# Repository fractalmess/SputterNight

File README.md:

# SputterNight
Consolidated efforts towards refurbishing a Edwards 306 sputter tool in oakland Ca

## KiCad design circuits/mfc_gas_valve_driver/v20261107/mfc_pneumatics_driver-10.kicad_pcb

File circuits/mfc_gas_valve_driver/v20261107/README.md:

Update to the MFC, front panel and pneumatic valve driver and interface circuit.
Analog support for the Tylan MFC added.

KiCad 10.0 used with this circuit.

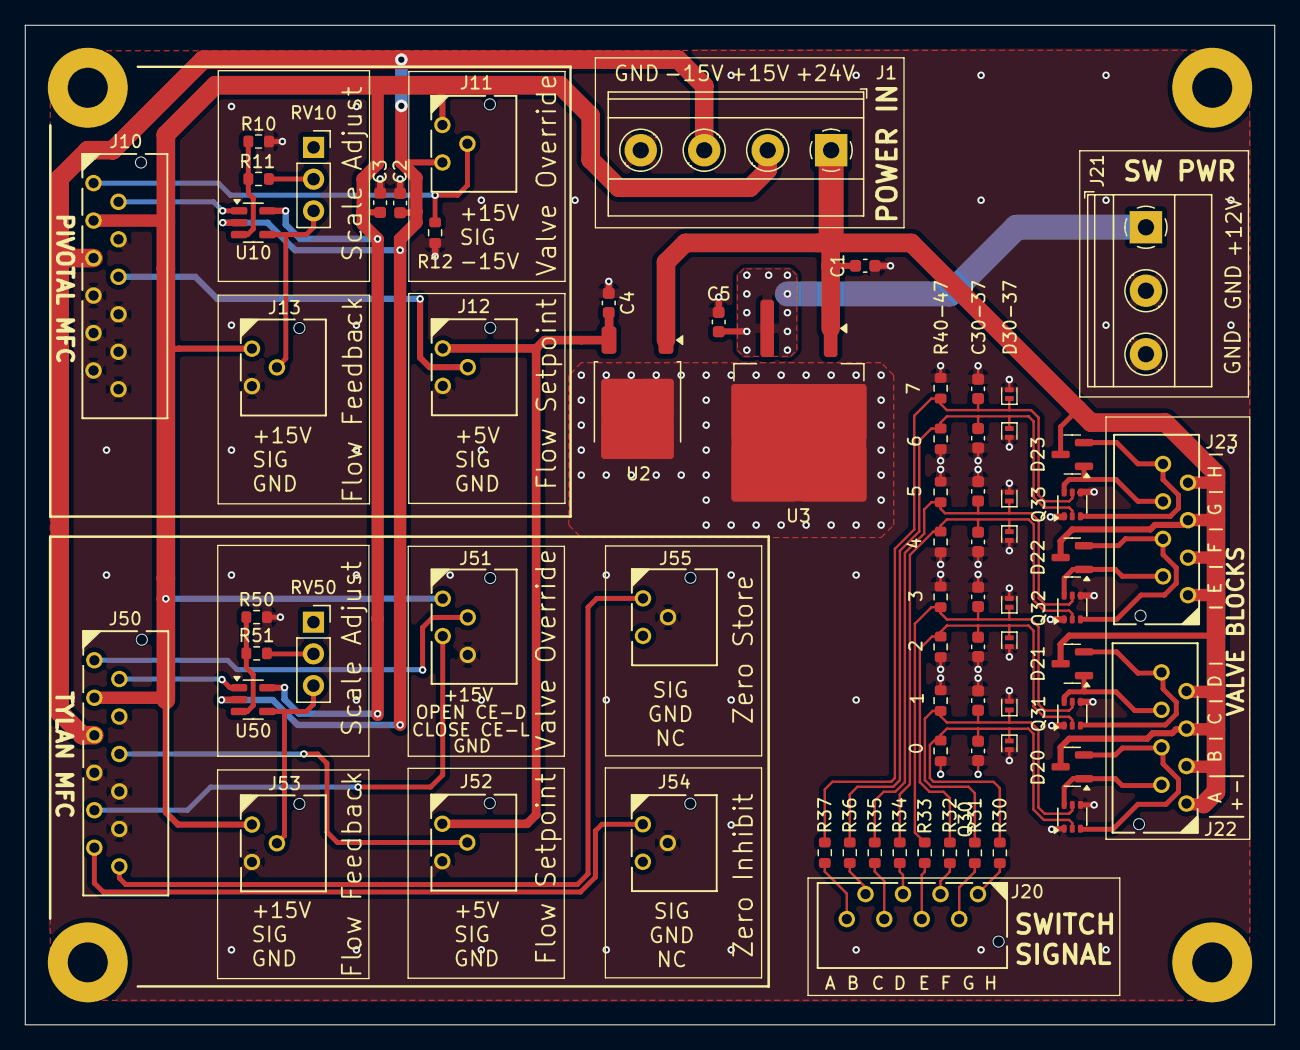
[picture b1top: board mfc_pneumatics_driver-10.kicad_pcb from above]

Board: 2 copper layers, 100.0 x 80.0 mm, 76 parts (1 on the bottom side), 45 nets.

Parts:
**REF: rfix_logo
C1, C2, C3, C4, C5: 1u 50V X7R; C_0603_1608Metric
C30, C31, C32, C33, C34, C35, C36, C37: C; C_0603_1608Metric
D20, D21, D22, D23: BAT54C; SOT-23
D30, D31, D32, D33, D34, D35, D36, D37: DF2S16CT; D_SOD-882
H1, H2, H3, H4: MountingHole_Pad; MountingHole_3.2mm_M3_Pad
J1: Screw_Terminal_01x04; TerminalBlock_Phoenix_MKDS-1,5-4-5.08_1x04_P5.08mm_Horizont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
J10, J50: Conn_01x12_Socket; Molex_CLIK-Mate_50315908_1x12-1MP_P1.50mm_Vertical
J11, J12, J13, J52, J53, J54, J55: Conn_01x03_Socket; Molex_CLIK-Mate_50315908_1x03-1MP_P1.50mm_Vertical
J20, J22, J23: Conn_01x08_Socket; Molex_CLIK-Mate_50315908_1x08-1MP_P1.50mm_Vertical
J21: Screw_Terminal_01x03; TerminalBlock_Phoenix_MKDS-1,5-3-5.08_1x03_P5.08mm_Horizont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
J51: Conn_01x04_Socket; Molex_CLIK-Mate_50315908_1x04-1MP_P1.50mm_Vertical
Q30, Q31, Q32, Q33: SSM6N7002KFU; SOT-363_SC-70-6
R10, R50: 1k; R_0603_1608Metric
R11, R51: 953R; R_0603_1608Metric
R12, R40, R41, R42, R43, R44, R45, R46, R47: 10k; R_0603_1608Metric
R30, R31, R32, R33, R34, R35, R36, R37: 10R; R_0603_1608Metric
RV10, RV50: 100R; PinSocket_1x03_P2.54mm_Vertical
U2: MC78M05_TO252; TO-252-2
U3: MC7812-TO263; TO-263-2
U10, U50: LM321; SOT-23-5

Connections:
+5V: C4.1, J12.1, J52.1, U2.3 (VO)
+12V: C5.1, J21.1, U3.3 (VO)
+15V: C3.1, J1.2, J10.3, J11.1, J13.1, J50.3, J51.1, J53.1, U10.5 (V+), U50.5 (V+)
+24V: C1.1, D20.3, D21.3, D22.3, D23.3, J1.1, J22.1, J22.3, J22.5, J22.7, J23.1, J23.3, J23.5, J23.7, U2.1 (VI), U3.1 (VI)
-15V: C2.2, J1.3, J10.5, J11.3, J50.5, U10.2 (V-), U50.2 (V-)
/SW1: J20.1, R30.1
/SW2: J20.2, R31.1
/SW3: J20.3, R32.1
/SW4: J20.4, R33.1
/SW5: J20.5, R34.1
/SW6: J20.6, R35.1
/SW7: J20.7, R36.1
/SW8: J20.8, R37.1
/valve_driver_1/V1_RETURN: D20.1, J22.2, Q30.6 (D)
/valve_driver_1/V2_RETURN: D20.2, J22.4, Q30.3 (D)
/valve_driver_2/V1_RETURN: D21.1, J22.6, Q31.6 (D)
/valve_driver_2/V2_RETURN: D21.2, J22.8, Q31.3 (D)
/valve_driver_3/V1_RETURN: D22.1, J23.2, Q32.6 (D)
/valve_driver_3/V2_RETURN: D22.2, J23.4, Q32.3 (D)
/valve_driver_4/V1_RETURN: D23.1, J23.6, Q33.6 (D)
/valve_driver_4/V2_RETURN: D23.2, J23.8, Q33.3 (D)
GND: C1.2, C2.1, C3.2, C4.2, C5.2, C30.2, C31.2, C32.2, C33.2, C34.2, C35.2, C36.2, C37.2, D30.2 (A), D31.2 (A), D32.2 (A), D33.2 (A), D34.2 (A), D35.2 (A), D36.2 (A), D37.2 (A), J1.4, J10.4, J10.7, J10.8, J10.9, J10.10, J10.11, J10.12, J12.3, J13.3, J21.2, J21.3, J50.4, J50.7, J50.8, J50.10, J51.4, J52.3, J53.3, J54.2, J55.2, Q30.1 (S), Q30.4 (S), Q31.1 (S), Q31.4 (S), Q32.1 (S), Q32.4 (S), Q33.1 (S), Q33.4 (S), R10.1, R12.2, R40.1, R41.1, R42.1, R43.1, R44.1, R45.1, R46.1, R47.1, R50.1, U2.2 (GND), U3.2 (GND)
unnamed: C30.1, D30.1 (K), Q30.2 (G), R30.2, R40.2
unnamed: C31.1, D31.1 (K), Q30.5 (G), R31.2, R41.2
unnamed: C32.1, D32.1 (K), Q31.2 (G), R32.2, R42.2
unnamed: C33.1, D33.1 (K), Q31.5 (G), R33.2, R43.2
unnamed: C34.1, D34.1 (K), Q32.2 (G), R34.2, R44.2
unnamed: C35.1, D35.1 (K), Q32.5 (G), R35.2, R45.2
unnamed: C36.1, D36.1 (K), Q33.2 (G), R36.2, R46.2
unnamed: C37.1, D37.1 (K), Q33.5 (G), R37.2, R47.2
unnamed: J10.1, J11.2, R12.1
unnamed: J10.2, U10.1 (+)
unnamed: J10.6, J12.2
unnamed: J13.2, RV10.3, U10.4
unnamed: J50.1, J51.2
unnamed: J50.2, U50.1 (+)
unnamed: J50.6, J52.2
unnamed: J50.9, J51.3
unnamed: J50.11, J54.1
unnamed: J50.12, J55.1
unnamed: J53.2, RV50.3, U50.4
unnamed: R11.2, RV10.2
unnamed: R51.2, RV50.2
unnamed: R10.2, R11.1, U10.3 (-)
unnamed: R50.2, R51.1, U50.3 (-)

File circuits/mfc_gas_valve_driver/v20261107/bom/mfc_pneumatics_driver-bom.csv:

"Id";"Designator";"Footprint";"Quantity";"Designation";"Supplier and ref";
1;"J50,J10";"Molex_CLIK-Mate_50315908_1x12-1MP_P1.50mm_Vertical";2;"Conn_01x12_Socket";;;
2;"RV50,RV10";"PinSocket_1x03_P2.54mm_Vertical";2;"100R";;;
3;"R50,R10";"R_0603_1608Metric";2;"1k";;;
4;"J55,J54,J53,J52,J13,J12,J11";"Molex_CLIK-Mate_50315908_1x03-1MP_P1.50mm_Vertical";7;"Conn_01x03_Socket";;;
5;"J51";"Molex_CLIK-Mate_50315908_1x04-1MP_P1.50mm_Vertical";1;"Conn_01x04_Socket";;;
6;"J23,J22,J20";"Molex_CLIK-Mate_50315908_1x08-1MP_P1.50mm_Vertical";3;"Conn_01x08_Socket";;;
7;"U50,U10";"SOT-23-5";2;"LM321";;;
8;"R51,R11";"R_0603_1608Metric";2;"953R";;;
9;"R37,R34,R31,R32,R35,R33,R36,R30";"R_0603_1608Metric";8;"10R";;;
10;"D22,D20,D21,D23";"SOT-23";4;"BAT54C";;;
11;"R40,R42,R46,R41,R47,R12,R43,R45,R44";"R_0603_1608Metric";9;"10k";;;
12;"C2,C1,C5,C4,C3";"C_0603_1608Metric";5;"1u 50V X7R";;;
13;"J1";"TerminalBlock_Phoenix_MKDS-1,5-4-5.08_1x04_P5.08mm_Horizontal";1;"Screw_Terminal_01x04";;;
14;"Q31,Q33,Q32,Q30";"SOT-363_SC-70-6";4;"SSM6N7002KFU";;;
15;"J21";"TerminalBlock_Phoenix_MKDS-1,5-3-5.08_1x03_P5.08mm_Horizontal";1;"Screw_Terminal_01x03";;;
16;"D31,D35,D33,D37";"D_SOD-882";4;"DF2S16CT";;;
17;"U2";"TO-252-2";1;"MC78M05_TO252";;;
18;"U3";"TO-263-2";1;"MC7812-TO263";;;
